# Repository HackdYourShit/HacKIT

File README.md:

# HacKIT
a low to high tech civic privacy hard(wear) kit for the reclaiming, redesigning, and hacking of the Amazon Echo, Google Home, Apple Siri.

Go [here](https://www.instructables.com/id/HacKIT-a-Civic-Privacy-Hardwear-Kit-for-Hacking-Al/) for a step-by-step build guide for HacKIT.

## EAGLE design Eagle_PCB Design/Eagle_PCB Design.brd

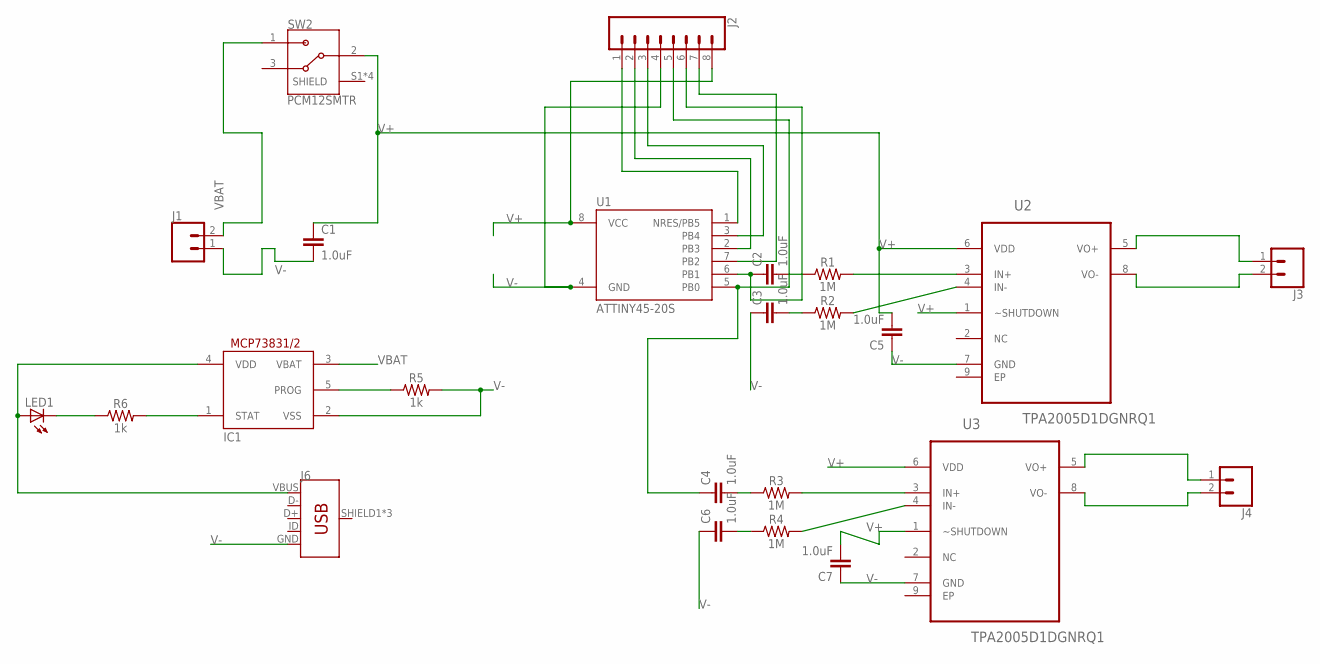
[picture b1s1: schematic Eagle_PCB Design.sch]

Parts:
C1, C2, C3, C4, C5, C6, C7: 1.0uF; 0603
IC1: MCP73831/OT; SOT23-5L
J1, J3, J4: CONN_02PTH3; 1X02_LONGPADS
J2: CONN_08NO_SILK_FEMALE_PTH; 1X08_NO_SILK
J6: USB_MICRO-B_FEMALE-SMT; USB-B-MICRO-SMD
LED1: LEDCHIPLED_0603; CHIPLED_0603
R1, R2, R3, R4: 1M; 0603
R5, R6: 1k; 0603
SW2: PCM12SMTR; SW_PCM12SMTR
U1: ATTINY45-20S; SOIC8_EIAJ_208MIL
U2, U3: TPA2005D1DGNRQ1; SOP65P490X110-9N

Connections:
unnamed: C2.2, R1.1
unnamed: R1.2, U2.3 (IN+)
unnamed: J3.1, U2.5 (VO+)
unnamed: J3.2, U2.8 (VO-)
unnamed: C2.1, J2.6, U1.6 (PB1)
unnamed: R2.2, U2.4 (IN-)
unnamed: C3.2, R2.1
unnamed: C6.2, R4.1
unnamed: J2.1, U1.1 (NRES/PB5)
unnamed: J2.2, U1.2 (PB3)
unnamed: J2.3, U1.3 (PB4)
unnamed: IC1.4 (VDD), J6.VBUS, LED1.A
unnamed: J4.1, U3.5 (VO+)
unnamed: J2.7, U1.7 (PB2)
unnamed: J4.2, U3.8 (VO-)
unnamed: R3.2, U3.3 (IN+)
unnamed: R4.2, U3.4 (IN-)
unnamed: C4.2, R3.1
unnamed: C4.1, J2.5, U1.5 (PB0)
unnamed: IC1.5 (PROG), R5.1
unnamed: LED1.C, R6.1
unnamed: IC1.1 (STAT), R6.2
V+: C1.1, C5.2, C7.2, J2.8, SW2.2, U1.8 (VCC), U2.1 (~SHUTDOWN), U2.6 (VDD), U3.1 (~SHUTDOWN), U3.6 (VDD)
V-: C1.2, C3.1, C5.1, C6.1, C7.1, IC1.2 (VSS), J1.1, J2.4, J6.GND, R5.2, U1.4 (GND), U2.7 (GND), U3.7 (GND)
VBAT: IC1.3 (VBAT), J1.2, SW2.1

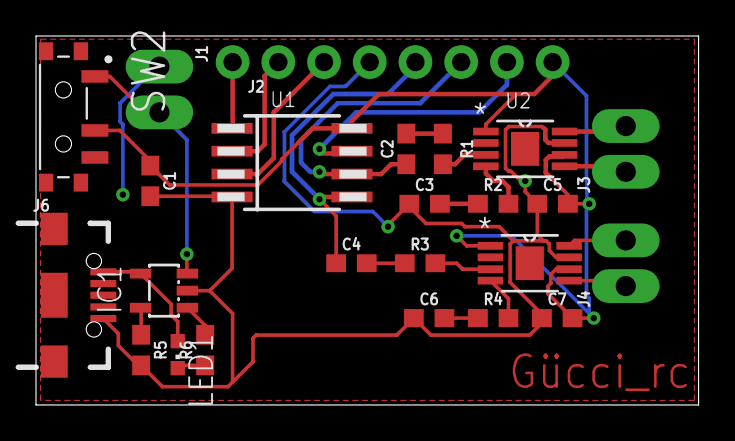
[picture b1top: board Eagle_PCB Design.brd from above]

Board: 2 copper layers, 36.8 x 20.5 mm, 24 parts (0 on the bottom side), 25 nets.

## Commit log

2020-07-14 Create Audio Samples
2020-07-15 created folders
2020-07-15 Edited folder names
2020-07-15 Eagle PCB Design
2020-07-15 HacKIT image
2020-07-15 Remove hackit image
2020-07-15 hackit image trying again
2020-07-15 Project Logo
2020-07-15 Remove
2020-07-15 Audio Samples

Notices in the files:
parts and their libraries:
SparkFun-Capacitors: Licensing: Creative Commons ShareAlike 4.0 International - https://creativecommons.org/licenses/by-sa/4.0
